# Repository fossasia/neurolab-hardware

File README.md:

# Neurolab Hardware

Repository for Neurolab Open Hardware platform.

We are developing a neuro-device to collect brainwaves as a headband with integrated electronics. This repository holds the PCB schematics and layouts for the Neurolab Hardware. 

Front Side               | Back Side
 ----------------------- | ---------------------------
 | 

## Buy

* You can get the device in future from the [FOSSASIA Shop](https://fossasia.com).
* More resellers will be listed on the [PSLab website](https://pslab.io/shop/).

## Communication

* The Neurolab [chat channel is on Gitter](https://gitter.im/fossasia/neurolab).
* Please also join us on the [Mailing List](https://groups.google.com/forum/#!forum/pslab-fossasia).

## Goal and Roadmap
The goal of the Neurolab project is to develop an easy to use open hardware measurement headset device for brain waves that can be plugged into an Android smartphone and a software application and enables us to understand our brains better.

Our brains communicate through neurotransmitters and their activity emits electricity. The neuroheadset measures that electricity on the skin of the forehead and the software processes the signal so that it can translated into a visual or auditory representation. The data that can be collected can be analysed to identify mental health, stress, relaxation and even diseases like Alzheimer. 

Current devices in the medical industry are usually not accessible by doctors due to their high pricing. They are also complicated to use. The idea of the device is to integrate it into a headband and focus on signals that can be obtained through the frontal lobe.

A difference to existing projects like OpenBCI is that it will not be necessary to 3D print large headsets. Instead we are focusing on creating a device that collects as much data as possible through the forehead. To achieve this goal we are using high-grade sensors and flexible electronics.

## License

This project is licensed under the Apache License 2.0. A copy of [LICENSE](LICENSE) is to be present along with the source code. To obtain the software under a different license, please contact FOSSASIA.

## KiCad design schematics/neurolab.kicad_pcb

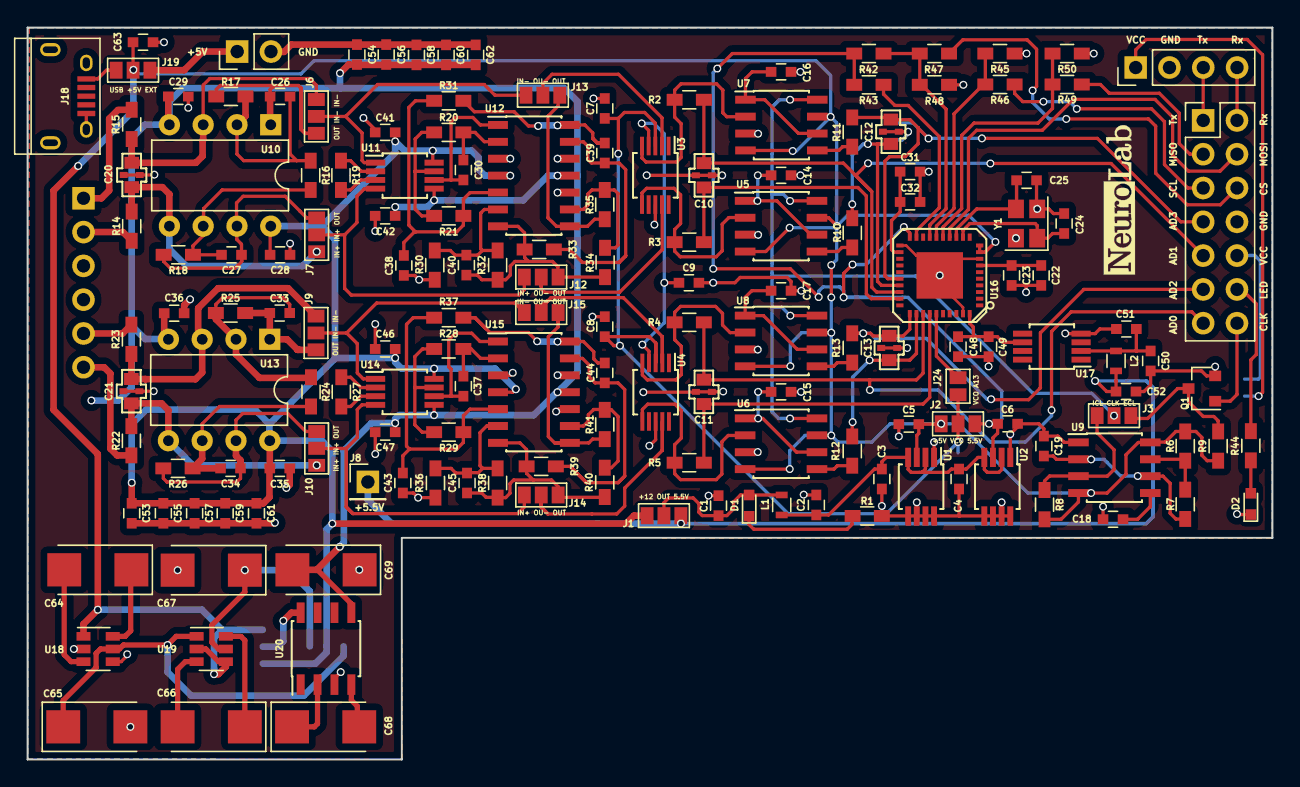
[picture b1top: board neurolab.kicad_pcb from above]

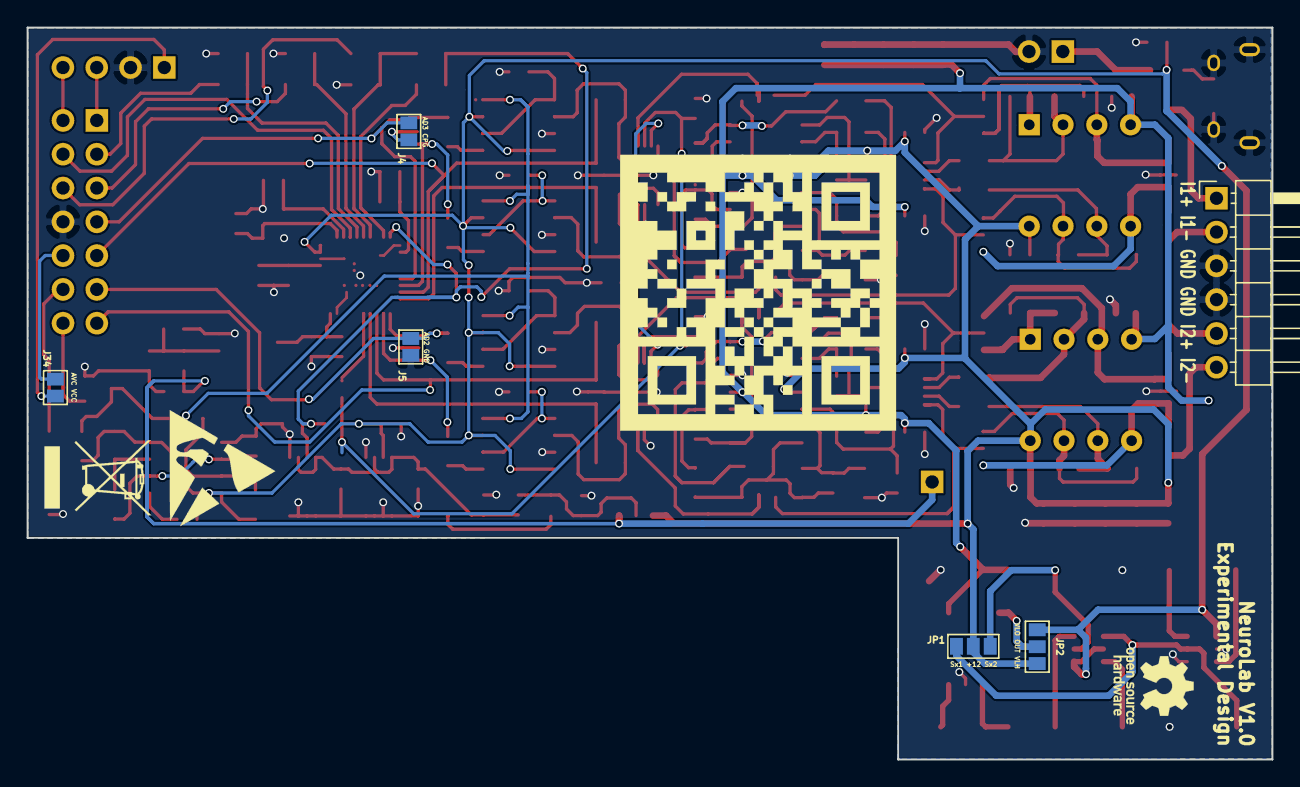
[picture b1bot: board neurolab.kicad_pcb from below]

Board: 2 copper layers, 93.6 x 55.0 mm, 169 parts (6 on the bottom side), 119 nets.

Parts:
C1, C2, C3, C4, C7, C8, C9, C41, C42, C46, C47, C48, C51, C52, C53, C54, C55, C56, C57, C58, C59, C60: 2.2u; C_0603
C5, C6, C63: 4.7u; C_0603
C10, C11, C12, C13: 0.1u; Decouple_Cap_0603
C14, C15, C16, C17, C18, C23, C28, C29, C31, C35, C36, C49, C50, C61, C62: 0.1u; C_0603
C19: 2.2n; C_0603
C20, C21: 1n; Decouple_Cap_0603
C22, C30, C32, C37, C39, C44: 1u; C_0603
C24, C25: 8pF; C_0603
C26, C27, C33, C34: 4.7n; C_0603
C38, C40, C43, C45: 47p; C_0603
C64, C65, C66, C67, C68, C69: 100u; CP_Tantalum_Case-C_EIA-6032-28_Reflow
D1: Blue; LED_0603
D2: LED_ALT; LED_0603
J1, J2, J3, J6, J7, J9, J10, J12, J13, J14, J15, J19: GS3
J4, J5, J24, J34: GS2
J8: 5.5V; Pin_Header_Straight_1x01_Pitch2.54mm
J11: ProMini; Pin_Header_Straight_2x07_Pitch2.54mm
J16: Channel; Pin_Header_Angled_1x06_Pitch2.54mm
J17: External; Pin_Header_Straight_1x02_Pitch2.54mm
J18: USB_OTG; USB_Micro-B
J32: Bluetooth; Pin_Header_Straight_1x04_Pitch2.54mm
JP1: VoltOut; GS3
JP2: VVV; GS3
L1, L2: BLM15HB121SN1; L_0603
Q1: 2N7002; SOT-23
R1: 20k; R_0603_HandSoldering
R2, R3, R4, R5, R14, R15, R22, R23: 4.7k; R_0603_HandSoldering
R6, R46, R47, R49: 1k; R_0603_HandSoldering
R7, R17, R18, R25, R26, R34, R35, R40, R41: 100k; R_0603_HandSoldering
R8, R9, R42, R43: 10k; R_0603_HandSoldering
R10, R11, R12, R13: 470; R_0603_HandSoldering
R16, R24, R45, R48, R50: 2k; R_0603_HandSoldering
R19, R27: 200; R_0603_HandSoldering
R20, R28, R31, R32, R33, R37, R38, R39: 1M; R_0603_HandSoldering
R21, R29, R30, R36: 4.02k; R_0603_HandSoldering
R44: 5.1k; R_0603_HandSoldering
U1: ADP1720ARMZ-5; MSOP-8_3x3mm_Pitch0.65mm
U2: ADP1720ARMZ-3.3; MSOP-8_3x3mm_Pitch0.65mm
U3, U4: AD8475; MSOP-10_3x3mm_Pitch0.5mm
U5, U6, U7, U8: MAX7480ESA+; SOIC-8_3.9x4.9mm_Pitch1.27mm
U9: TLC555CD; SOIC-8_3.9x4.9mm_Pitch1.27mm
U10, U13: OPA2111KP; DIP-8_W7.62mm
U11, U14: AD8422ARMZ; MSOP-8_3x3mm_Pitch0.65mm
U12, U15: OP4117; SOIC-14_3.9x8.7mm_Pitch1.27mm
U16: AD7173; LFCSP-40-1EP
U17: ADR445BR; MSOP-8_3x3mm_Pitch0.65mm
U18, U19: TC1240A; SOT-23-6
U20: 7660; SOIC-8_3.9x4.9mm_Pitch1.27mm
Y1: FA-20H; Crystal_SMD_SeikoEpson_FA238-4pin_3.2x2.5mm

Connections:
+3V: C6.1, J2.1, R42.2, R43.2, U2.3, U16.20
+5.5V: C52.1, J1.1, J8.1, L2.2
+5V: C5.1, C63.1, J2.3, J19.2, JP2.3, R6.1, R8.1, R9.1, U1.3, U5.4, U5.7, U6.4, U6.7, U7.4, U7.7, U8.4, U8.7, U9.4, U9.8, U16.9, U16.10, U18.1, U19.2, U19.4
+12V: C28.2, C35.2, C41.1, C46.1, C53.1, C55.1, C57.1, C59.1, C61.1, J1.3, JP1.2, JP2.1, U10.8, U11.8, U12.4, U13.8, U14.8, U15.4
-12V: C29.1, C36.1, C42.1, C47.1, C54.2, C56.2, C58.2, C60.2, C62.2, C69.2, U10.4, U11.5, U12.11, U13.4, U14.5, U15.11, U20.5
/ADConverter/AIN4: C12.3, R10.2, U16.27
/ADConverter/AIN6: C13.3, R12.2, U16.32
/ADConverter/AIN13: J24.1, U16.35
/ADConverter/CS: R42.1, R47.2, R48.1, U16.17
/ADConverter/DI: R49.2, R50.1, U16.15
/ADConverter/SCL: R45.1, R46.2, U16.16
/Amplifier Block 1/IN+: J16.2, R14.1
/Amplifier Block 1/IN-: J16.1, R15.1
/Amplifier Block 2/IN+: J16.6, R22.1
/Amplifier Block 2/IN-: J16.5, R23.1
/Attenuator/+IN0.4XA: J12.2, U3.9
/Attenuator/+IN0.4XB: J14.2, U4.9
/Attenuator/+OUTA: R2.2, U3.5, U7.2
/Attenuator/+OUTB: R4.2, U4.5, U8.2
/Attenuator/-IN0.4XA: J13.2, U3.2
/Attenuator/-IN0.4XB: J15.2, U4.2
/Attenuator/-OUTA: R3.2, U3.6, U5.2
/Attenuator/-OUTB: R5.2, U4.6, U6.2
/Clock Block/CLK: J3.2, U5.8, U6.8, U7.8, U8.8
/External Power/VIN: C2.1, C3.1, C4.1, L1.2, U1.2, U1.4, U2.2, U2.4
/RC Filter 1/-OUTA': C10.1, R3.1, U16.29
/RC Filter 1/-OUTB': C11.1, R5.1, U16.34
/RC Filter 2/IN1: R10.1, U5.5
/RC Filter 2/IN2: R11.1, U7.5
/RC Filter 2/IN3: R12.1, U6.5
/RC Filter 2/IN4: R13.1, U8.5
AD0: C11.3, J11.13, R4.1, U16.33
AD1: C10.3, J11.9, R2.1, U16.28
AD2: C13.1, J5.2, J11.11, R13.2, U16.31
AD3: C12.1, J4.2, J11.7, R11.2, U16.26
CS: J11.6, R47.1
EXCLK: J11.14, Q1.1
GND: C1.2, C2.2, C3.2, C4.2, C5.2, C6.2, C7.2, C8.2, C9.2, C10.2, C11.2, C13.2, C14.2, C15.2, C16.2, C17.2, C18.2, C19.2, C20.2, C21.2, C22.2, C23.2, C24.2, C25.2, C28.1, C29.2, C31.2, C32.2, C35.1, C36.2, C38.2, C41.2, C42.2, C43.2, C46.2, C47.2, C48.2, C49.2, C50.2, C51.2, C52.2, C53.2, C54.1, C55.2, C56.1, C57.2, C58.1, C59.2, C60.1, C61.2, C62.1, C63.2, C65.2, C67.2, C69.1, D2.1, J5.1, J11.8, J16.3, J16.4, J17.2, J18.5, J18.6, J32.2, Q1.2, R1.2, R30.1, R36.1, R45.2, R48.2, R50.2, U1.1, U1.5, U1.6, U1.7, U1.8, U2.1, U2.5, U2.6, U2.7, U2.8, U3.8, U4.8, U5.3, U6.3, U7.3, U8.3, U9.1, U12.3, U12.10, U12.12, U15.3, U15.10, U15.12, U16.8, U16.21, U16.39, U16.41, U17.4, U18.2, U18.4, U20.3, Y1.2, Y1.4
MISO: J11.3, R49.1
MOSI: J11.4, U16.14
unnamed: C1.1, D1.2, J1.2, L1.1
unnamed: C9.1, U3.4, U4.4
unnamed: C12.2, J4.1
unnamed: C14.1, U5.1, U5.6
unnamed: C15.1, U6.1, U6.6
unnamed: C16.1, U7.1, U7.6
unnamed: C17.1, U8.1, U8.6
unnamed: C18.1, U9.5
unnamed: C19.1, R7.2, U9.2, U9.6
unnamed: C20.1, J6.1, R15.2, U10.3
unnamed: C20.3, J7.3, R14.2, U10.5
unnamed: C21.1, J9.1, R23.2, U13.3
unnamed: C21.3, J10.3, R22.2, U13.5
unnamed: C22.1, C23.1, U16.7
unnamed: C24.1, U16.12, Y1.1
unnamed: C25.1, U16.13, Y1.3
unnamed: C26.1, J6.3, R17.1, U10.1
unnamed: C26.2, R16.1, R17.2, U10.2
unnamed: C27.1, J7.1, R18.2, U10.7
unnamed: C27.2, R16.2, R18.1, U10.6
unnamed: C30.1, R20.2, U12.2
unnamed: C30.2, U11.6, U12.1
unnamed: C31.1, C32.1, U16.22
unnamed: C33.1, J9.3, R25.1, U13.1
unnamed: C33.2, R24.1, R25.2, U13.2
unnamed: C34.1, J10.1, R26.2, U13.7
unnamed: C34.2, R24.2, R26.1, U13.6
unnamed: C37.1, R28.2, U15.2
unnamed: C37.2, U14.6, U15.1
unnamed: C38.1, R21.2, R31.2, U12.5
unnamed: C39.1, R33.2, U12.13
unnamed: C39.2, R31.1, U12.14
unnamed: C40.1, J12.1, R32.1, R33.1, R34.2, U12.7
unnamed: C40.2, R30.2, R32.2, U12.6
unnamed: C43.1, R29.2, R37.2, U15.5
unnamed: C44.1, R39.2, U15.13
unnamed: C44.2, R37.1, U15.14
unnamed: C45.1, J14.1, R38.1, R39.1, R40.2, U15.7
unnamed: C45.2, R36.2, R38.2, U15.6
unnamed: C48.1, C49.1, U16.40, U17.6
unnamed: C50.1, C51.1, L2.1, U17.2
unnamed: C64.1, U18.6
unnamed: C64.2, U18.3
unnamed: C65.1, JP1.3, U18.5, U19.1
unnamed: C66.1, U19.6
unnamed: C66.2, U19.3
unnamed: C67.1, JP1.1, U19.5
unnamed: C68.1, U20.2
unnamed: C68.2, U20.4
unnamed: D1.1, R1.1
unnamed: D2.2, R44.2
unnamed: J3.1, R8.2, U9.3
unnamed: J3.3, Q1.3, R9.2
unnamed: J10.2, J14.3, U14.4
unnamed: J11.10, J34.2
unnamed: J11.12, R44.1
unnamed: J7.2, J12.3, U11.4
unnamed: J6.2, J13.1, U11.1
unnamed: J13.3, R35.1, U12.8
unnamed: J9.2, J15.1, U14.1
unnamed: J15.3, R41.1, U15.8
unnamed: J17.1, J19.1
unnamed: J18.1, J19.3
unnamed: JP2.2, U20.8
unnamed: R6.2, R7.1, U9.7
unnamed: R19.1, U11.3
unnamed: R19.2, U11.2
unnamed: R20.1, R21.1, U11.7
unnamed: R27.1, U14.3
unnamed: R27.2, U14.2
unnamed: R28.1, R29.1, U14.7
unnamed: R34.1, R35.2, U12.9
unnamed: R40.1, R41.2, U15.9
unnamed: R43.1, U16.19
RxI: J11.2, J32.4
SCL: J11.5, R46.1
TxO: J11.1, J32.3
VCC: J32.1, J34.1
VCCIO: C7.1, C8.1, J2.2, J24.2, U3.3, U4.3

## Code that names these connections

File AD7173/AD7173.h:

/*
===================================================================================
library to control the AD7173 ADC

                              G    A    A    A    A    A    A
                    R    R    P    I    I    I    I    I    I    A
                    E    E    I    N    N    N    N    N    N    I
                    F    F    O    1    1    1    1    1    1    N
                    +    -    3    5    4    3    2    1    0    9
                    |    |    |    |    |    |    |    |    |    |
                _________________________________________________________
              /    40.  39.  38.  37.  36.  35.  34.  33.  32.  31.     |
             |                                                          |
     AIN16 --| 1.                                                   30. |-- AIN8
AIN0/REF2- --| 2.                                                   29. |-- AIN7
AIN1/REF2+ --| 3.                                                   28. |-- AIN6
      AIN2 --| 4.                                                   27. |-- AIN5
      AIN3 --| 5.                                                   26. |-- AIN4
    REFOUT --| 6.                                                   25. |-- GPIO2
   REGCAPA --| 7.                                                   24. |-- GPIO1
      AVSS --| 8.                                                   23. |-- GPIO0
     AVDD1 --| 9.                                                   22. |-- REGCAPD
     AVDD2 --| 10.                                                  21. |-- DGND
             |                                                          |
             |     11.  12.  13.  14.  15.  16.  17.  18.  19.  20.     |
             |__________________________________________________________|
                    |    |    |    |    |    |    |    |    |    |
                    P    X    X    D    D    S    C    E    S    I
                    D    T    T    O    I    C    S    R    Y    O
                    S    A    A    U    N    L         R    N    V
                    W    L    L    T         K         O    C    D
                    1    2                             R         D
                         /
                         C
                         L
                         K
                         I
                         O
===================================================================================
*/

#ifndef _AD7173_H_INCLUDED
#define _AD7173_H_INCLUDED

#include "SPI.h"

#if ARDUINO >= 100
#include "Arduino.h"
#else
#include "WProgram.h"
#endif

/* enable or disable debug */
#define DEBUG_ENABLED 0

/* delay for reading and writing registers  */
#define READ_WRITE_DELAY 1

/* ADC channel registers */
#define CH0 0x10
#define CH1 0x11
#define CH2 0x12
#define CH3 0x13
#define CH4 0x14
#define CH5 0x15
#define CH6 0x16
#define CH7 0x17
#define CH8 0x18
#define CH9 0x19
#define CH10 0x1A
#define CH11 0x1B
#define CH12 0x1C
#define CH13 0x1D
#define CH14 0x1E
#define CH15 0x1F

/* ADC analog input registers */
#define AIN0 0x00
#define AIN1 0x01
#define AIN2 0x02
#define AIN3 0x03
#define AIN4 0x04
#define AIN5 0x05
#define AIN6 0x06
#define AIN7 0x07
#define AIN8 0x08
#define AIN9 0x09
#define AIN10 0x0A
#define AIN11 0x0B
#define AIN12 0x0C
#define AIN13 0x0D
#define AIN14 0x0E
#define AIN15 0x0F
#define AIN16 0x10

/* ADC gain registers */
#define GAIN0 0x38
#define GAIN1 0x39
#define GAIN2 0x3A
#define GAIN3 0x3B
#define GAIN4 0x3C
#define GAIN5 0x3D
#define GAIN6 0x3E
#define GAIN7 0x3F

/* ADC setup config register */
#define SETUP0 0x20
#define SETUP1 0x21
#define SETUP2 0x22
#define SETUP3 0x23
#define SETUP4 0x24
#define SETUP5 0x25
#define SETUP6 0x26
#define SETUP7 0x27

/* ADC filter config registers */
#define FILTER0 0x28
#define FILTER1 0x29
#define FILTER2 0x2A
#define FILTER3 0x2B
#define FILTER4 0x2C
#define FILTER5 0x2D
#define FILTER6 0x2E
#define FILTER7 0x2F

/* ADC offset registers */
#define OFFSET0 0x30
#define OFFSET1 0x31
#define OFFSET2 0x32
#define OFFSET3 0x33
#define OFFSET4 0x34
#define OFFSET5 0x35
#define OFFSET6 0x36
#define OFFSET7 0x37

/* ADC filter speed values (samples per second) */
#define SPS_1 0x16
#define SPS_2 0x15
#define SPS_5 0x14
#define SPS_10 0x13
#define SPS_16 0x12
#define SPS_20 0x11
#define SPS_50 0x10
#define SPS_60 0x0F
#define SPS_100 0x0E
#define SPS_200 0x0D
#define SPS_381 0x0C
#define SPS_504 0x0B
#define SPS_1007 0x0A
#define SPS_2597 0x09
#define SPS_5208 0x08
#define SPS_10417 0x07
#define SPS_15625 0x06
#define SPS_31250 0x00

/* other ADC registers */
#define ID_REG 0x07
#define DATA_REG 0x04
#define COMMS_REG 0x00
#define IFMODE_REG 0x02
#define STATUS_REG 0x00
#define ADCMODE_REG 0x01
#define GPIOCON_REG 0x06
#define REGCHECK_REG 0x03

/* other ADC channel input registers */
#define REF_POS 0x15
#define REF_NEG 0x16
#define TEMP_SENSOR_POS 0x11
#define TEMP_SENSOR_NEG 0x12

/* ADC setup coding modes */
#define BIPOLAR 1
#define UNIPOLAR 0

/* ADC data conversion modes */
#define CONTINUOUS_READ_MODE 0
#define SINGLE_CONVERSION_MODE 1
#define CONTINUOUS_CONVERSION_MODE 2

/* ADC data ready indicator */
#define DATA_READY digitalRead(MISO) == LOW

class AD7173Class {
public:
	/*
	=====================================
	constructor
	set default ADC setup coding mode
	set default ADC data conversion mode
	=====================================
	*/
	AD7173Class() : m_adc_data_mode(CONTINUOUS_CONVERSION_MODE), m_adc_setup_coding_output(BIPOLAR) {
		/* ... */
	}

	/*
	============================================
	initializes the SPI connection with the ADC
	@return bool - is ADC ID valid
	============================================
	*/
	bool init();

	/*
	==================================================
	cancels the current transaction to resync the ADC
	==================================================
	*/
	void resync();

	/*
	==============================================
	resets the ADC registers to the default state
	==============================================
	*/
	void reset();

	/*
	=====================================
	enables or disables ADC channels
	@param byte - channel register
	@param bool - enable or disable
	@param byte - optional analog input 1
	@param byte - optional analog input 2
	@return int - error code
	=====================================
	*/
	int enable_channel(byte, bool, byte = NULL, byte = NULL);

	/*
	==========================================
	sets the ADC filters data conversion rate
	@param byte - filter register
	@param byte - speed of conversion
	@return int - error code
	==========================================
	*/
	int set_filter_speed(byte, byte);

	/*
	==========================================
	enables the ADC filters  enhancement
	@param byte - filter register
	@param bool - enable or disable
	@param byte - configuration
	@return int - error code
	==========================================
	*/
	int enable_filter_enhancement(byte, bool, byte = NULL);

	/*
	================================
	sets the ADC setups coding mode
	@param byte - setup register
	@param int - coding mode
	@return int - error code
	================================
	*/
	int set_setup_coding(byte, int);

	/*
	=========================
	sets the ADC data mode
	@param int - data mode
	@return int - error code
	=========================
	*/
	int set_data_mode(int);

	/*
	==========================================
	gets the ADC conversion result
	@return byte[] - the ADC conversion result
	==========================================
	*/
	int get_data(byte *);

	/*
	=============================================
	gets the current conversion results channel
	@param byte - current data channel
	@return int - error code
	=============================================
	*/
	int get_current_data_channel(byte &);

private:
	/* ADC data mode */
	int m_adc_data_mode;

	/* ADC setup coding mode */
	int m_adc_setup_coding_output;

	/*
	===========================
	print bytes in nice format
	@param byte - byte to print
	===========================
	*/
	void print_byte(byte);

	/*
	=========================================
	writes to a desired ADC register
	@param byte - the register where to write
	@param  byte[] - the bytes to write
	@param int - the length of bytes to write
	=========================================
	*/
	int write_register(byte, byte *, int);

	/*
	=============================================
	reads from a desired ADC register
	@param byte - the register to read
	@param int - the length of bytes to read
	@return byte[] - the ADC register read result
	=============================================
	*/
	int read_register(byte, byte *, int);
};

extern AD7173Class AD7173;

#endif

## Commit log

2014-04-26 AD7173-8.py added debug messages
2014-04-26 AD7173-8.ino refactoring + read and write registers
2014-04-26 AD7173-8.py added 1 - 3 bit debugging functions
2014-04-26 AD7173-8.ino added register defines, updated debugging
2014-04-29 AD7173-8.ino added speed and conversion mode functions
2014-04-29 AD7173-8.py updated offset binary calculation
2014-04-29 bipolar.ino removed obsolete
2014-04-30 Update AD7173-8.ino
    updated chip illustration
2014-05-03 AD7173-8.ino added channel enable/disable function
2014-05-03 AD7173-8.ino updated speed, mode and channel functions
2014-05-03 AD7173-8.ino fixed enable_adc_channel
2014-05-04 AD7173-8.ino improved debuging
2014-05-06 AD7173-8.ino updated adc_data_mode
2014-05-06 AD7173-8.ino fixed adc_data_mode
2014-05-13 AD7173-*.* renamed files
2014-05-13 AD7173.lbr added eagle library
2014-05-13 AD7173.py renamed file
2014-05-13 AD7173.pdf renamed file
2014-05-13 AD7173.ino refactor + added setup coding output
2014-05-13 README.md update
2014-05-13 AD7173.ino added get current adc data channel
2014-05-17 schematics/* added eagle schematics files for the ADC
2014-05-22 schematics/AD7173.lbr updated AD7173 eagle library
2014-05-22 AD7173.ino fixed enable_adc_channel AINs
2014-05-22 AD7173/* create arduino library, renamed schematics
2014-05-22 AD7173.ino removed obsolete file
2014-05-24 AD7173/AD7173.* contructor for default values
2014-05-26 AD7173/keywords.txt updated keywords
2014-05-26 AD7173/examples/Basic/Basic.ino udated basic example
2014-05-26 AD7173/AD7173.cpp/.h refactor + fixed enabling channels
2014-06-12 datasheets/ added datasheets folder
2014-06-12 circuits/* updated eagle circuits
2014-06-12 AD7173.pdf removed obsolete file
2014-07-02 AD7173/AD7173.cpp fixed enable_channel ain1
2014-07-02 AD7173.* added enable_filter_enhancement
2014-07-26 circuits/AD7173/* moved AD7173 circuit to it's own folder
2014-07-26 circuits/amplifier/* added amplifier circuit
2015-03-18 updated aplifier circuit
2015-03-18 updated gitignore
2015-04-11 added ADC test code for raspberry pi
2015-04-11 upadted AD7173 circuits
2015-04-11 upadted raspberry pi code
2015-06-27 added adr44X datasheet
2015-06-27 updated AD7173 circuit
2015-06-28 added ferrite bean datasheet
2015-06-28 updated AD7173 breakout board
2015-07-03 upadted AD7173 breakout board
2015-07-04 updated git ignore
2015-07-29 added set_clock_mode
2015-07-29 folder restructure
2015-08-19 refactoring code, enhanced debug
2015-08-20 changed coding mode func name
2015-08-20 updated raspberry pi library
2015-08-24 renamed files
2015-08-24 refactoring
2015-08-24 added sending data over bluetooth
2015-09-03 made pads longer
2015-09-03 updated pins, components placing
2015-09-05 small margin updates
2015-09-05 updated ignore
2015-09-05 updated label
2016-01-11 Update LICENSE
    changed to CC BY SA
2016-01-11 Added instructions for adding tasks
2016-01-11 Included corresponding task
2016-01-11 Added approved task
2016-01-11 Add Node.js GitHub OAuth
2016-01-11 Light out:javascript Task uploaded.
2016-01-11 Added my tasks for GCI
2016-01-12 Create Index.html
    Index file for the lights out task. Standalone
2016-01-12 Added the Index.html for Google CGI
2016-01-12 Revert "Added the Index.html for Google CGI"
    This reverts commit 200c518c136bad4b05d299c9e74db4a0a3626aa3.
2016-01-12 Improved website.
2016-01-12 Updated my task for Google CGI
2016-01-12 The screenshots
    Whoops, looks like I forgot to add them in the first shot
2016-01-12 Update LICENSE
    can't change license now, changed it back ^_^
2016-01-13 Fix preview links
2016-01-13 My project
2016-01-14 typo
2016-01-15 Added my task code
2016-01-15 Added Tweets_Retriver task -Yathannsh
2016-01-17 Added my file
2016-01-19 My Task Files
2016-01-19 Update AD7173.cpp
    fix: enable_channel, value wrongly shifted
2016-01-19 geolocation
2016-01-20 Get geolocation by Lee Wei Jie
2016-01-20 Improve design and UI and display message if user rejects location request
2016-01-23 Added my projects
2016-01-23 Add [Hangman]_[Sawyer_Charles]
2016-01-24 Added all my Projects
2016-01-25 added hangman
2016-02-11 Added my projects!
2016-05-19 Update AD7173.cpp
    fixed set_clock_mode
2018-11-13 init: updated repo with new layouts
2018-11-14 refactor: reordered folder structure
2018-11-17 updated schematics
2018-11-18 added ADC Chip
2018-11-20 added arduino base
2018-11-21 added footprints
2018-11-21 complete schematics
2018-11-21 added decouple capacitors
2018-11-24 pcb layout for amplifier block
2018-11-24 feat: power circuitry
2018-11-26 feat: attenuator and clock circuits
2018-11-27 feat: filter circuits
    refactor
2018-11-28 feat: ADC Circuit
2018-11-29 refactor: route improvements
2018-11-29 docs: updated readme
    typo
2018-11-29 docs: added BoM
2018-12-01 optimize: routing and placement
    optimize: squeeze space
    optimize: squeeze space contd.
    optimize: contd.
2018-12-03 optimize: component placement
2018-12-03 optimize: reduce spacing 20mils
2018-12-03 optimize: redundant foot prints
2018-12-03 optimize: routing to minimize length
2018-12-03 optimize: alternative route for +5V
2018-12-03 optimize: route parts
2018-12-03 optimize: removed redundant SPI connector
2018-12-03 optimize: routing SPI
2018-12-04 optimize: final routing
2019-03-26 feat: schematics and readme update
2020-03-27 Update LICENSE
2021-05-22 chore: updated gitignore file
2021-05-22 chore: updated gitignore file (#63)
2021-06-02 Optimized Routing and Fixed DRC
